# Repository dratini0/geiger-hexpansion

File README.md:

# Geiger counter hexpansion

## High voltage generator

The high voltage power supply uses a microcontroller PWM peripheral, and a uses an ADC for feedback.
This means that it can only work on the ADC side of the Tildagon.
It also means that the power supply is completely dependent on software.

## Buzzer

Instead of connecting the speaker directly to the pulse detector, it is attached to the MCU.
This way, the clicking can be muted in software.
Alternatively, there is a solder jumper to short.

## Acknowledgements

Uses the [hexpansion template from EMF](https://github.com/emfcamp/badge-2024-hardware/tree/main/hexpansion)

Schematic loosely based on [Mightyohm's](https://mightyohm.com/blog/products/geiger-counter/) and [BroHogan's](https://sites.google.com/site/diygeigercounter/home) designs.

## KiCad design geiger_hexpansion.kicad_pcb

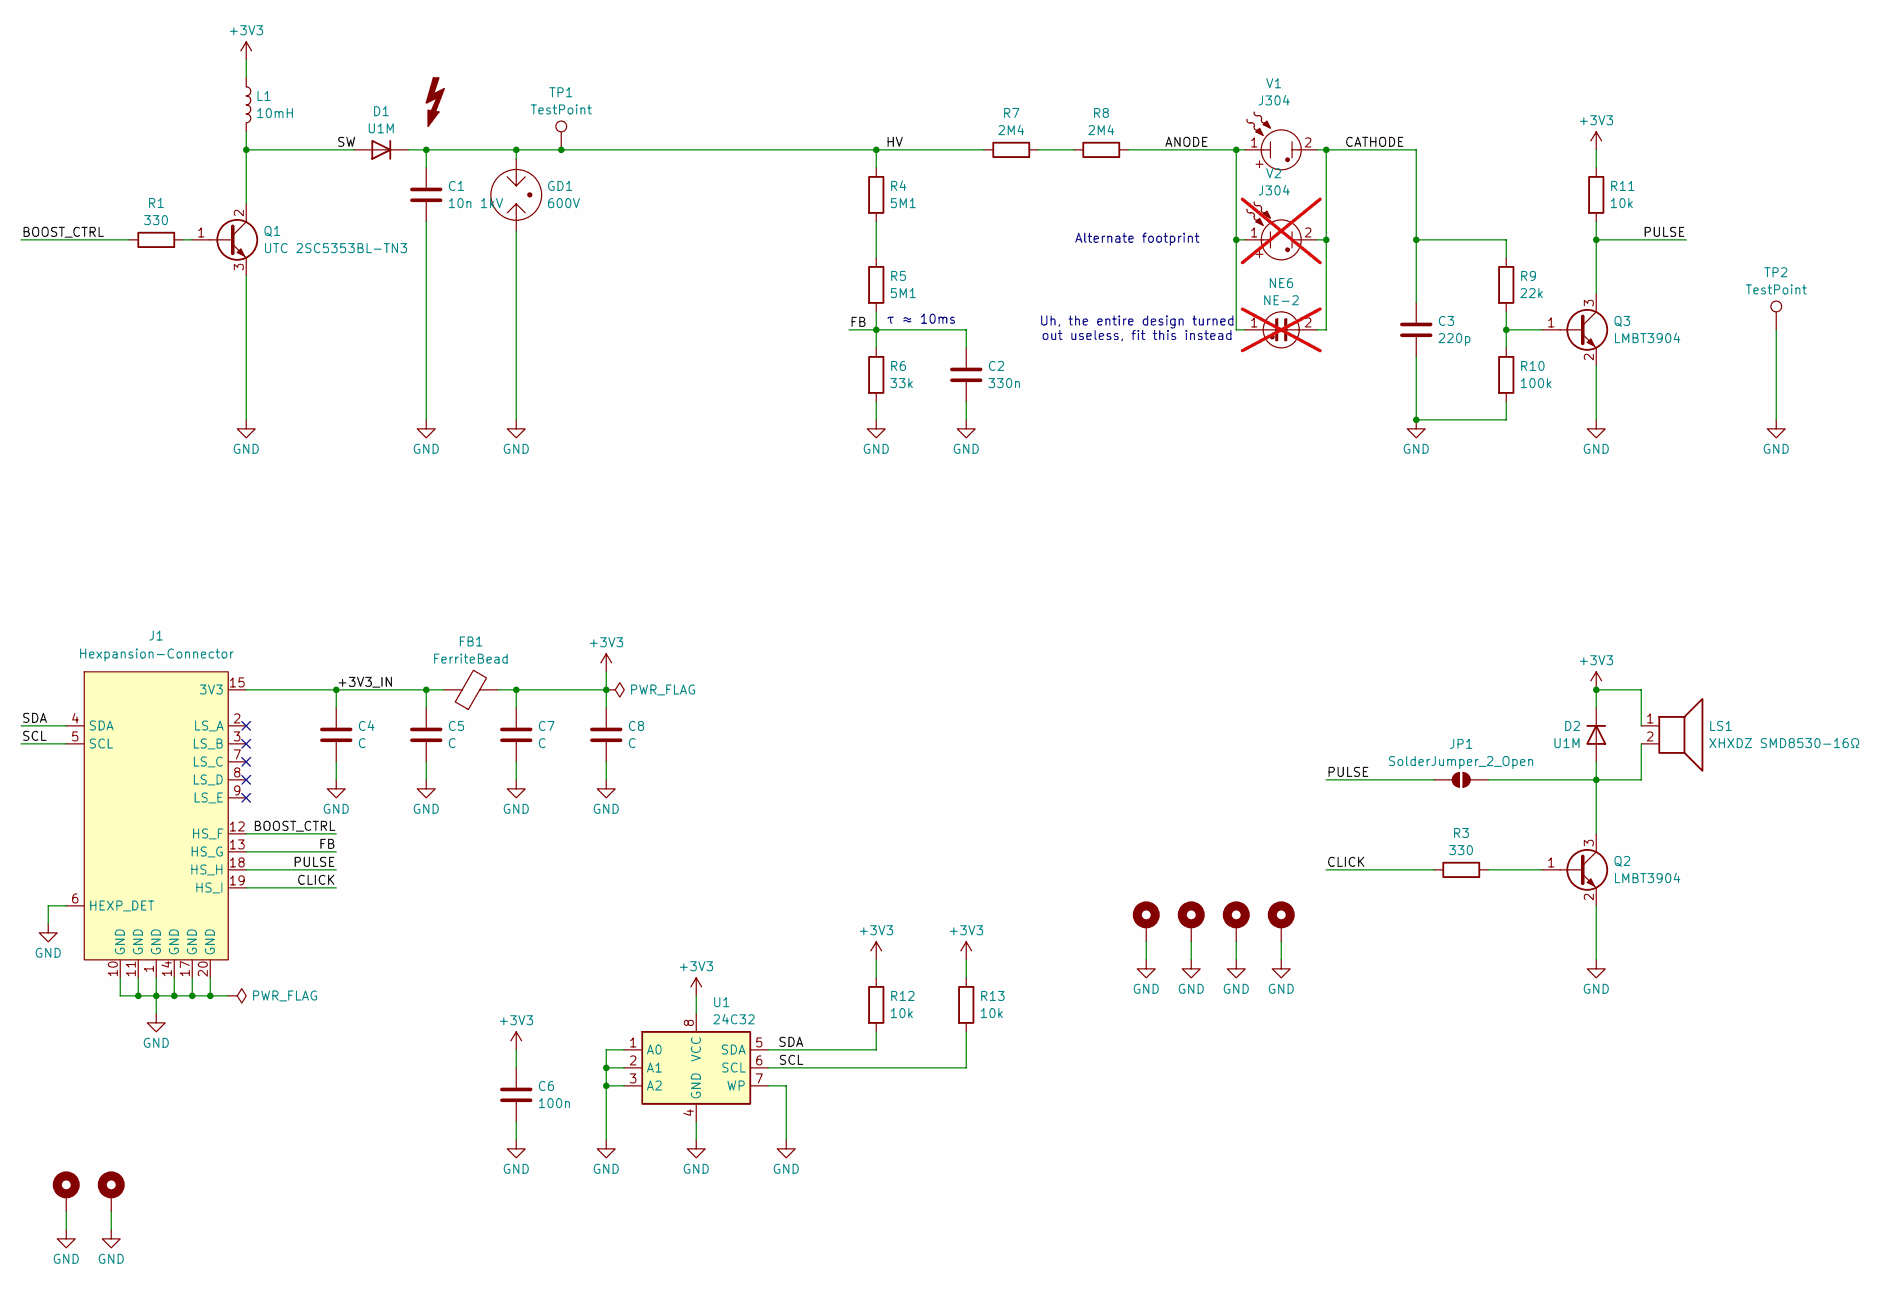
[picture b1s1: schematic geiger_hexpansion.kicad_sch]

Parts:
C1: 10n 1kV; C_1206_3216Metric_Pad1.33x1.80mm_HandSolder; LCSC C107192
C2: 330n; C_0805_2012Metric_Pad1.18x1.45mm_HandSolder
C3: 220p; C_0805_2012Metric_Pad1.18x1.45mm_HandSolder
C4, C5, C7, C8: C; C_0805_2012Metric_Pad1.18x1.45mm_HandSolder
C6: 100n; C_0805_2012Metric_Pad1.18x1.45mm_HandSolder
D1, D2: U1M; D_SOD-123F; LCSC C53222325
FB1: FerriteBead; L_0805_2012Metric_Pad1.05x1.20mm_HandSolder
GD1: 600V; 4532-601-LF; LCSC C41784202
H1, H2: MountingHole_Pad; MountingHole_2.2mm_M2_Pad_Via
H3, H4, H5, H6: MountingHole_Pad; MountingHole_3.2mm_M3_Pad_Via
J1: Hexpansion-Connector; hexpansion-edge-connector
JP1: SolderJumper_2_Open; SolderJumper-2_P1.3mm_Open_TrianglePad1.0x1.5mm
L1: 10mH; L_Ferrocore_DLG-0705; MPN ZE ZECD75-103K; LCSC C41422284
LS1: XHXDZ SMD8530-16Ω; XHXDZ_SMD8530; LCSC C49246948
NE6: NE-2; PinHeader_1x02_P2.54mm_Vertical; not fitted
Q1: UTC 2SC5353BL-TN3; TO-252-2; LCSC C73311
Q2, Q3: LMBT3904; SOT-23; LCSC C49580
R1, R3: 330; R_0805_2012Metric_Pad1.20x1.40mm_HandSolder
R4, R5: 5M1; R_1206_3216Metric_Pad1.30x1.75mm_HandSolder; LCSC C873653
R6: 33k; R_0805_2012Metric_Pad1.20x1.40mm_HandSolder
R7, R8: 2M4; R_1206_3216Metric_Pad1.30x1.75mm_HandSolder; LCSC C326957
R9: 22k; R_0805_2012Metric_Pad1.20x1.40mm_HandSolder
R10: 100k; R_0805_2012Metric_Pad1.20x1.40mm_HandSolder
R11, R12, R13: 10k; R_0805_2012Metric_Pad1.20x1.40mm_HandSolder
TP1, TP2: TestPoint; TestPoint_Pad_D1.5mm
U1: 24C32; SOIC-8_3.9x4.9mm_P1.27mm
V1: J304; E10_SMD
V2: J304; E10_THT; not fitted

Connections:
+3V3: C6.1, C7.1, C8.1, D2.1 (K), FB1.2, L1.1, LS1.1, R11.1, R12.1, R13.1, U1.8 (VCC)
/+3V3_IN: C4.1, C5.1, FB1.1, J1.15 (3V3), J1.16 (3V3)
/ANODE: NE6.1, R8.2, V1.1, V2.1
/BOOST_CTRL: J1.12 (HS_F), R1.1
/CATHODE: C3.1, NE6.2, R9.1, V1.2, V2.2
/CLICK: J1.19 (HS_I), R3.1
/FB: C2.1, J1.13 (HS_G), R5.2, R6.1
/HV: C1.1, D1.1 (K), GD1.3, R4.1, R7.1, TP1.1 (1_1)
/PULSE: J1.18 (HS_H), JP1.1 (A), Q3.3 (C), R11.2
/SCL: J1.5 (SCL), R13.2, U1.6 (SCL)
/SDA: J1.4 (SDA), R12.2, U1.5 (SDA)
/SW: D1.2 (A), L1.2, Q1.2 (C)
GND: C1.2, C2.2, C3.2, C4.2, C5.2, C6.2, C7.2, C8.2, GD1.1, H1.1 (1_1), H2.1 (1_1), H3.1 (1_1), H4.1 (1_1), H5.1 (1_1), H6.1 (1_1), J1.1 (GND), J1.6 (HEXP_DET), J1.10 (GND), J1.11 (GND), J1.14 (GND), J1.17 (GND), J1.20 (GND), Q1.3 (E), Q2.2 (E), Q3.2 (E), R6.2, R10.2, TP2.1 (1_1), U1.1 (A0), U1.2 (A1), U1.3 (A2), U1.4 (GND), U1.7 (WP)
unnamed: D2.2 (A), JP1.2 (B), LS1.2, Q2.3 (C)
unnamed: Q1.1 (B), R1.2
unnamed: Q2.1 (B), R3.2
unnamed: Q3.1 (B), R9.2, R10.1
unnamed: R4.2, R5.1
unnamed: R7.2, R8.1

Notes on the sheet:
Alternate footprint
τ ≈ 10ms
Uh, the entire design turned out useless, fit this instead

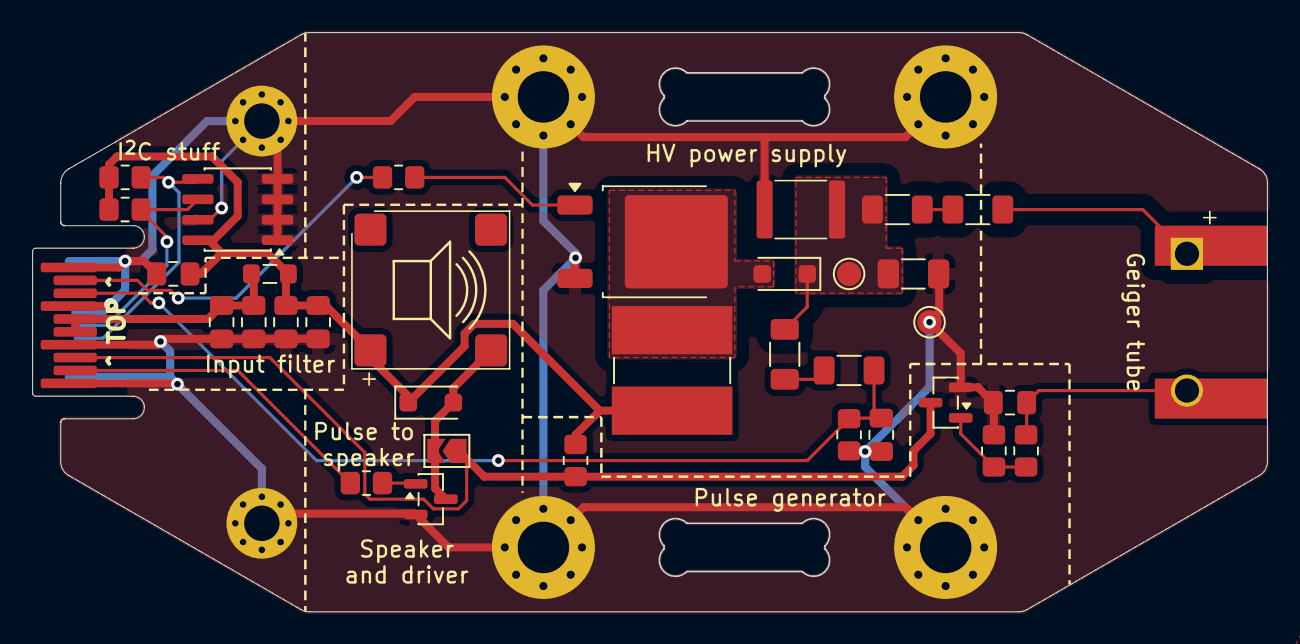
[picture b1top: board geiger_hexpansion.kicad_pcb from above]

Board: 2 copper layers, 76.8 x 36.0 mm, 42 parts (0 on the bottom side), 19 nets.
